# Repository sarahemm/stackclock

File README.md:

# stackclock
StackClock - Modular configurable high-accuracy desk clock

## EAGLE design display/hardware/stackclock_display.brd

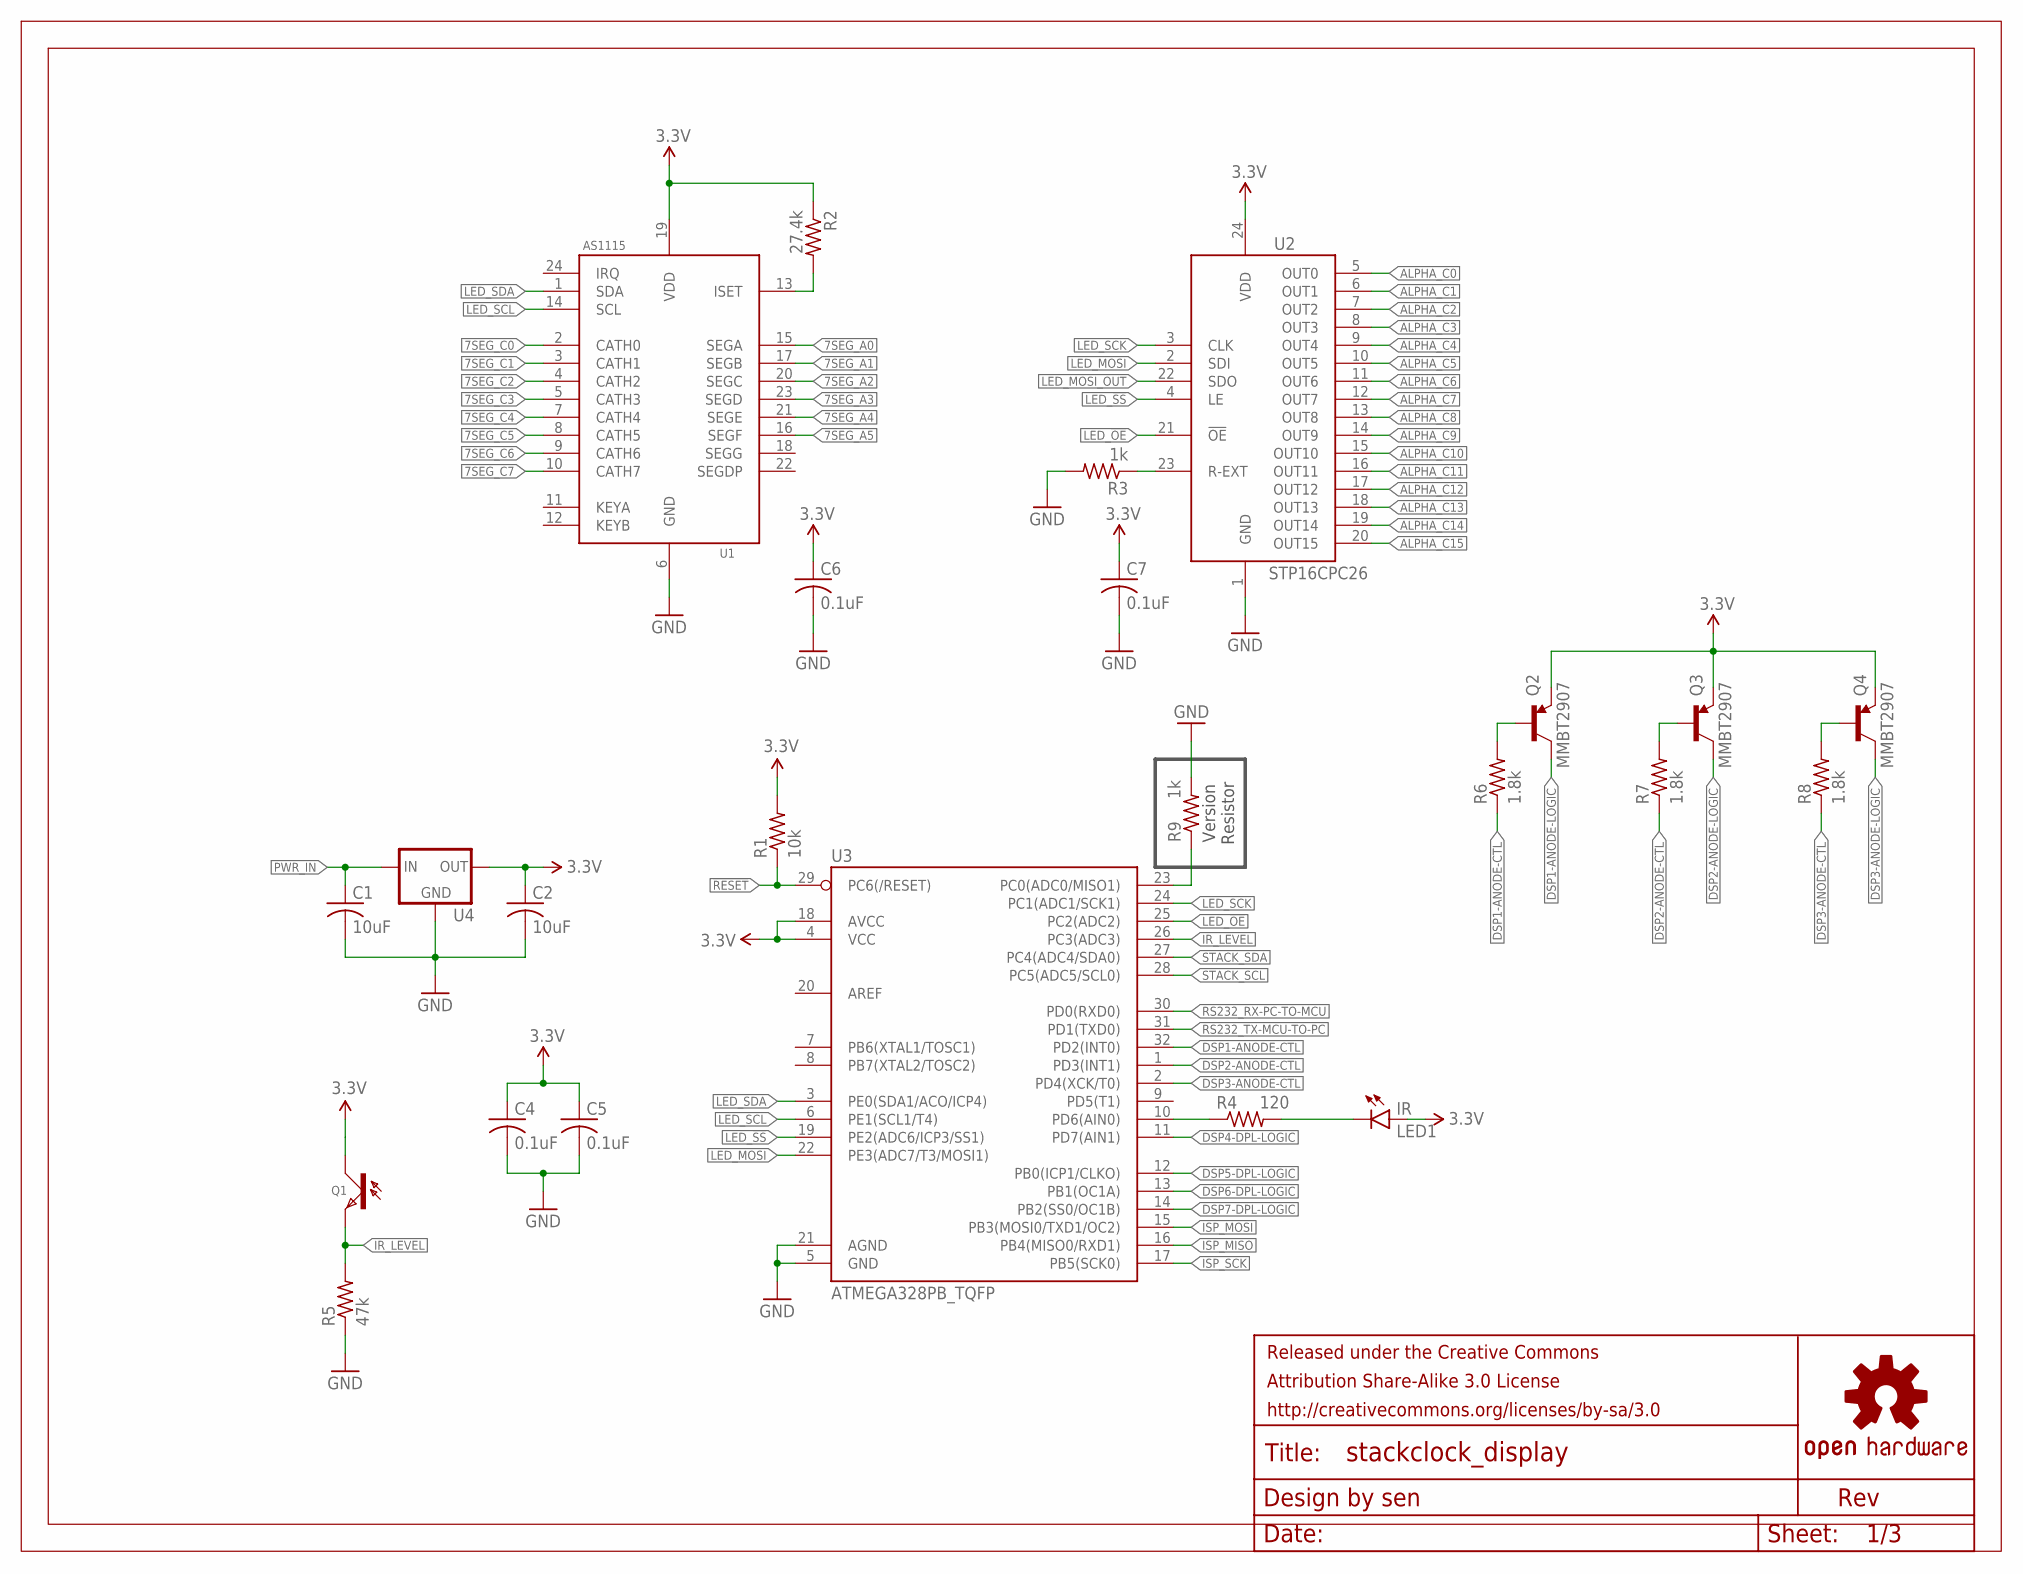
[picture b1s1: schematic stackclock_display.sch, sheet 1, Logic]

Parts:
C1, C2: 10uF; C0805
C4, C5, C6, C7: 0.1uF; C0603
FRAME1: FRAME-LETTER-GRID-OSHW-SENOSHW-LOGO-L; OSHW-LOGO-L
LED1: IR; LED-1206
Q1: PT15-21C/TR8; 1206_PHOTOTRANSISTOR
Q2, Q3, Q4: MMBT2907; SOT23-3
R1: 10k; R0603
R2: 27.4k; R0603
R3, R9: 1k; R0603
R4: 120; R0603
R5: 47k; R0603
R6, R7, R8: 1.8k; R0603
U1: AS1115; QSOP24
U2: STP16CPC26; TSSOP24
U3: ATMEGA328PB_TQFP; TQFP32-08
U4: NCP1117DT33G; DPAK

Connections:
3.3V: C2.1, C4.1, C5.1, C6.1, C7.1, LED1.A, Q1.C, Q2.2 (E), Q3.2 (E), Q4.2 (E), R1.2, R2.1, U1.19 (VDD), U2.24 (VDD), U3.4 (VCC), U3.18 (AVCC), U4.4 (OUT); also elsewhere on the board
7SEG_A0: U1.15 (SEGA); also elsewhere on the board
7SEG_A1: U1.17 (SEGB); also elsewhere on the board
7SEG_A2: U1.20 (SEGC); also elsewhere on the board
7SEG_A3: U1.23 (SEGD); also elsewhere on the board
7SEG_A4: U1.21 (SEGE); also elsewhere on the board
7SEG_A5: U1.16 (SEGF); also elsewhere on the board
7SEG_C0: U1.2 (CATH0); also elsewhere on the board
7SEG_C1: U1.3 (CATH1); also elsewhere on the board
7SEG_C2: U1.4 (CATH2); also elsewhere on the board
7SEG_C3: U1.5 (CATH3); also elsewhere on the board
7SEG_C4: U1.7 (CATH4); also elsewhere on the board
7SEG_C5: U1.8 (CATH5); also elsewhere on the board
7SEG_C6: U1.9 (CATH6); also elsewhere on the board
7SEG_C7: U1.10 (CATH7); also elsewhere on the board
!RESET: R1.1, U3.29 (PC6(/RESET)); also elsewhere on the board
ALPHA_C0: U2.5 (OUT0); also elsewhere on the board
ALPHA_C1: U2.6 (OUT1); also elsewhere on the board
ALPHA_C2: U2.7 (OUT2); also elsewhere on the board
ALPHA_C3: U2.8 (OUT3); also elsewhere on the board
ALPHA_C4: U2.9 (OUT4); also elsewhere on the board
ALPHA_C5: U2.10 (OUT5); also elsewhere on the board
ALPHA_C6: U2.11 (OUT6); also elsewhere on the board
ALPHA_C7: U2.12 (OUT7); also elsewhere on the board
ALPHA_C8: U2.13 (OUT8); also elsewhere on the board
ALPHA_C9: U2.14 (OUT9); also elsewhere on the board
ALPHA_C10: U2.15 (OUT10); also elsewhere on the board
ALPHA_C11: U2.16 (OUT11); also elsewhere on the board
ALPHA_C12: U2.17 (OUT12); also elsewhere on the board
ALPHA_C13: U2.18 (OUT13); also elsewhere on the board
ALPHA_C14: U2.19 (OUT14); also elsewhere on the board
ALPHA_C15: U2.20 (OUT15); also elsewhere on the board
DSP1-ANODE-CTL: R6.1, U3.32 (PD2(INT0))
DSP1-ANODE-LOGIC: Q2.3 (C); also elsewhere on the board
DSP1-ANODE-QR: Q2.1 (B), R6.2
DSP2-ANODE-CTL: R7.1, U3.1 (PD3(INT1))
DSP2-ANODE-LOGIC: Q3.3 (C); also elsewhere on the board
DSP2-ANODE-QR: Q3.1 (B), R7.2
DSP3-ANODE-CTL: R8.1, U3.2 (PD4(XCK/T0))
DSP3-ANODE-LOGIC: Q4.3 (C); also elsewhere on the board
DSP3-ANODE-QR: Q4.1 (B), R8.2
DSP4-DPL-LOGIC: U3.11 (PD7(AIN1)); also elsewhere on the board
DSP5-DPL-LOGIC: U3.12 (PB0(ICP1/CLKO)); also elsewhere on the board
DSP6-DPL-LOGIC: U3.13 (PB1(OC1A)); also elsewhere on the board
DSP7-DPL-LOGIC: U3.14 (PB2(SS0/OC1B)); also elsewhere on the board
GND: C1.2, C2.2, C4.2, C5.2, C6.2, C7.2, R3.2, R5.1, R9.2, U1.6 (GND), U2.1 (GND), U3.5 (GND), U3.21 (AGND), U4.1 (GND); also elsewhere on the board
HW_VERSION: R9.1, U3.23 (PC0(ADC0/MISO1))
IR_CTL: R4.1, U3.10 (PD6(AIN0))
IR_LEVEL: Q1.E, R5.2, U3.26 (PC3(ADC3)); also elsewhere on the board
IR_R: LED1.C, R4.2
ISP_MISO: U3.16 (PB4(MISO0/RXD1)); also elsewhere on the board
ISP_MOSI: U3.15 (PB3(MOSI0/TXD1/OC2)); also elsewhere on the board
ISP_SCK: U3.17 (PB5(SCK0)); also elsewhere on the board
LED_!OE: U2.21 (!OE), U3.25 (PC2(ADC2)); also elsewhere on the board
LED_!SS: U2.4 (LE), U3.19 (PE2(ADC6/ICP3/SS1)); also elsewhere on the board
LED_MOSI: U2.2 (SDI), U3.22 (PE3(ADC7/T3/MOSI1)); also elsewhere on the board
LED_MOSI_OUT: U2.22 (SDO); also elsewhere on the board
LED_SCK: U2.3 (CLK), U3.24 (PC1(ADC1/SCK1)); also elsewhere on the board
LED_SCL: U1.14 (SCL), U3.6 (PE1(SCL1/T4)); also elsewhere on the board
LED_SDA: U1.1 (SDA), U3.3 (PE0(SDA1/ACO/ICP4)); also elsewhere on the board
PWR_IN: C1.1, U4.3 (IN); also elsewhere on the board
RS232_RX-PC-TO-MCU: U3.30 (PD0(RXD0)); also elsewhere on the board
RS232_TX-MCU-TO-PC: U3.31 (PD1(TXD0)); also elsewhere on the board
STACK_SCL: U3.28 (PC5(ADC5/SCL0)); also elsewhere on the board
STACK_SDA: U3.27 (PC4(ADC4/SDA0)); also elsewhere on the board
U1-ISET: R2.2, U1.13 (ISET)
U2-REXT: R3.1, U2.23 (R-EXT)

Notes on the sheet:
Version Resistor

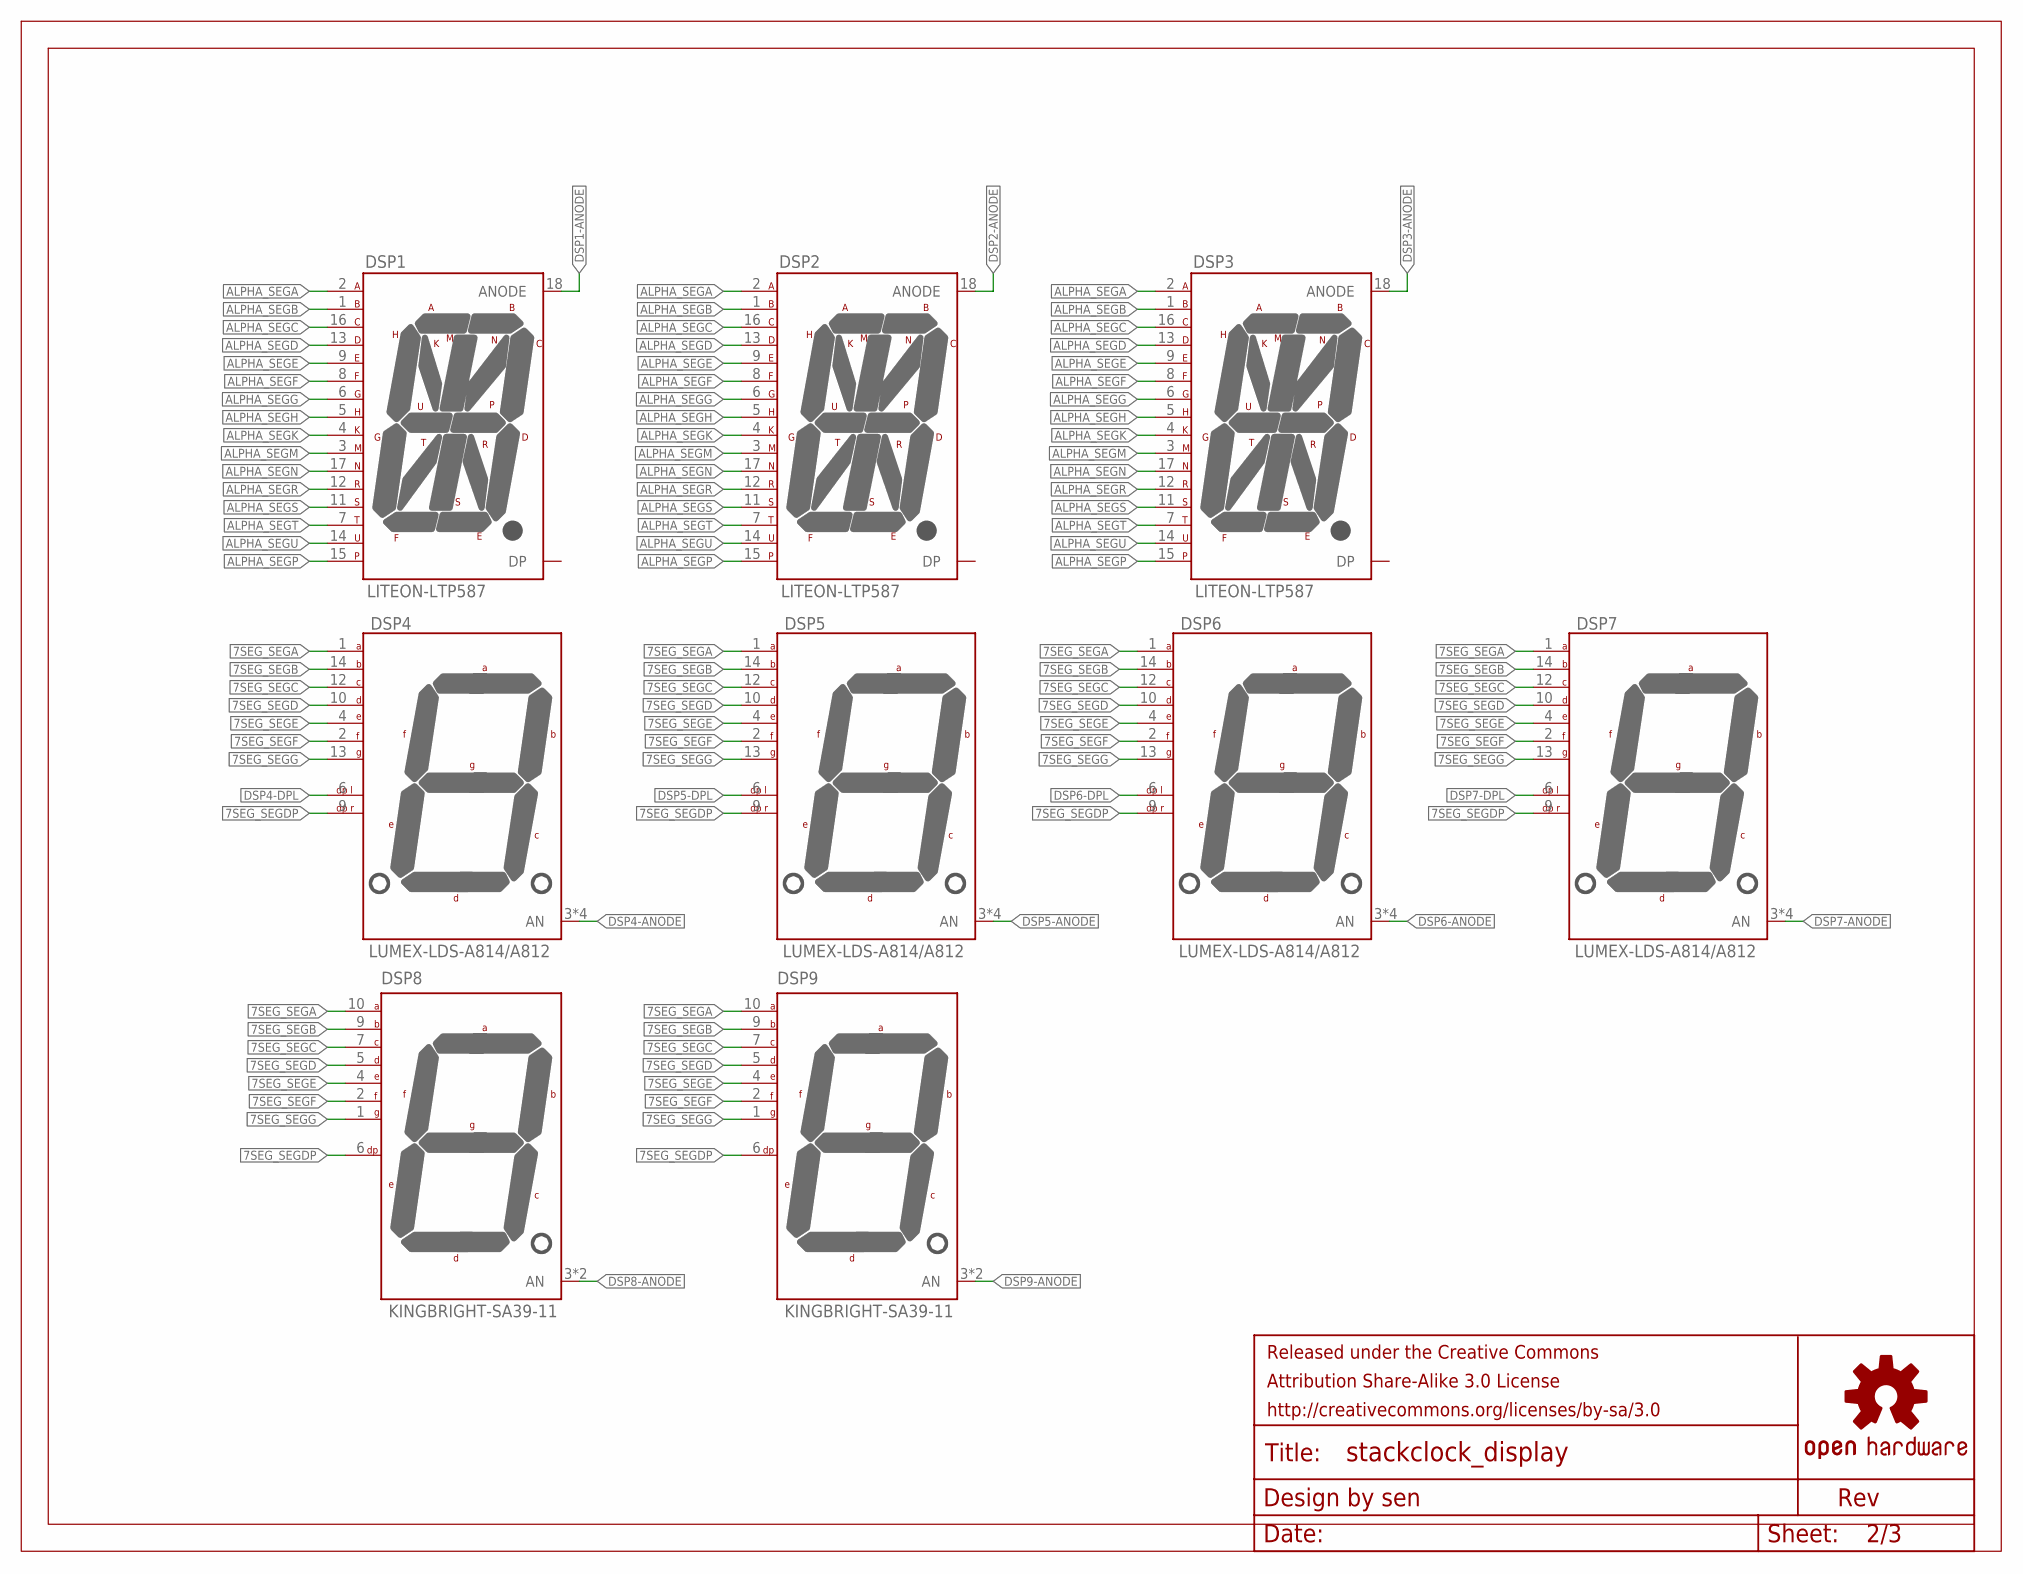
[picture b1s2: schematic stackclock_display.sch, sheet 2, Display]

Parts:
DSP1, DSP2, DSP3: LITEON-LTP587
DSP4, DSP5, DSP6, DSP7: LUMEX-LDS-A814/A812
DSP8, DSP9: KINGBRIGHT-SA39-11
FRAME2: FRAME-LETTER-GRID-OSHW-SENOSHW-LOGO-L; OSHW-LOGO-L

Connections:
7SEG_SEGA: DSP4.1 (A), DSP5.1 (A), DSP6.1 (A), DSP7.1 (A), DSP8.10 (A), DSP9.10 (A); also elsewhere on the board
7SEG_SEGB: DSP4.14 (B), DSP5.14 (B), DSP6.14 (B), DSP7.14 (B), DSP8.9 (B), DSP9.9 (B); also elsewhere on the board
7SEG_SEGC: DSP4.12 (C), DSP5.12 (C), DSP6.12 (C), DSP7.12 (C), DSP8.7 (C), DSP9.7 (C); also elsewhere on the board
7SEG_SEGD: DSP4.10 (D), DSP5.10 (D), DSP6.10 (D), DSP7.10 (D), DSP8.5 (D), DSP9.5 (D); also elsewhere on the board
7SEG_SEGDP: DSP4.9 (DP-R), DSP5.9 (DP-R), DSP6.9 (DP-R), DSP7.9 (DP-R), DSP8.6 (DP), DSP9.6 (DP); also elsewhere on the board
7SEG_SEGE: DSP4.4 (E), DSP5.4 (E), DSP6.4 (E), DSP7.4 (E), DSP8.4 (E), DSP9.4 (E); also elsewhere on the board
7SEG_SEGF: DSP4.2 (F), DSP5.2 (F), DSP6.2 (F), DSP7.2 (F), DSP8.2 (F), DSP9.2 (F); also elsewhere on the board
7SEG_SEGG: DSP4.13 (G), DSP5.13 (G), DSP6.13 (G), DSP7.13 (G), DSP8.1 (G), DSP9.1 (G); also elsewhere on the board
ALPHA_SEGA: DSP1.2 (A), DSP2.2 (A), DSP3.2 (A); also elsewhere on the board
ALPHA_SEGB: DSP1.1 (B), DSP2.1 (B), DSP3.1 (B); also elsewhere on the board
ALPHA_SEGC: DSP1.16 (C), DSP2.16 (C), DSP3.16 (C); also elsewhere on the board
ALPHA_SEGD: DSP1.13 (D), DSP2.13 (D), DSP3.13 (D); also elsewhere on the board
ALPHA_SEGE: DSP1.9 (E), DSP2.9 (E), DSP3.9 (E); also elsewhere on the board
ALPHA_SEGF: DSP1.8 (F), DSP2.8 (F), DSP3.8 (F); also elsewhere on the board
ALPHA_SEGG: DSP1.6 (G), DSP2.6 (G), DSP3.6 (G); also elsewhere on the board
ALPHA_SEGH: DSP1.5 (H), DSP2.5 (H), DSP3.5 (H); also elsewhere on the board
ALPHA_SEGK: DSP1.4 (K), DSP2.4 (K), DSP3.4 (K); also elsewhere on the board
ALPHA_SEGM: DSP1.3 (M), DSP2.3 (M), DSP3.3 (M); also elsewhere on the board
ALPHA_SEGN: DSP1.17 (N), DSP2.17 (N), DSP3.17 (N); also elsewhere on the board
ALPHA_SEGP: DSP1.15, DSP2.15, DSP3.15; also elsewhere on the board
ALPHA_SEGR: DSP1.12 (R), DSP2.12 (R), DSP3.12 (R); also elsewhere on the board
ALPHA_SEGS: DSP1.11 (S), DSP2.11 (S), DSP3.11 (S); also elsewhere on the board
ALPHA_SEGT: DSP1.7 (T), DSP2.7 (T), DSP3.7 (T); also elsewhere on the board
ALPHA_SEGU: DSP1.14 (U), DSP2.14 (U), DSP3.14 (U); also elsewhere on the board
DSP1-ANODE: DSP1.18 (ANODE); also elsewhere on the board
DSP2-ANODE: DSP2.18 (ANODE); also elsewhere on the board
DSP3-ANODE: DSP3.18 (ANODE); also elsewhere on the board
DSP4-ANODE: DSP4.3 (AN), DSP4.5 (AN), DSP4.11 (AN), DSP4.16 (AN); also elsewhere on the board
DSP4-DPL: DSP4.6 (DP-L); also elsewhere on the board
DSP5-ANODE: DSP5.3 (AN), DSP5.5 (AN), DSP5.11 (AN), DSP5.16 (AN); also elsewhere on the board
DSP5-DPL: DSP5.6 (DP-L); also elsewhere on the board
DSP6-ANODE: DSP6.3 (AN), DSP6.5 (AN), DSP6.11 (AN), DSP6.16 (AN); also elsewhere on the board
DSP6-DPL: DSP6.6 (DP-L); also elsewhere on the board
DSP7-ANODE: DSP7.3 (AN), DSP7.5 (AN), DSP7.11 (AN), DSP7.16 (AN); also elsewhere on the board
DSP7-DPL: DSP7.6 (DP-L); also elsewhere on the board
DSP8-ANODE: DSP8.3 (AN), DSP8.8 (AN); also elsewhere on the board
DSP9-ANODE: DSP9.3 (AN), DSP9.8 (AN); also elsewhere on the board

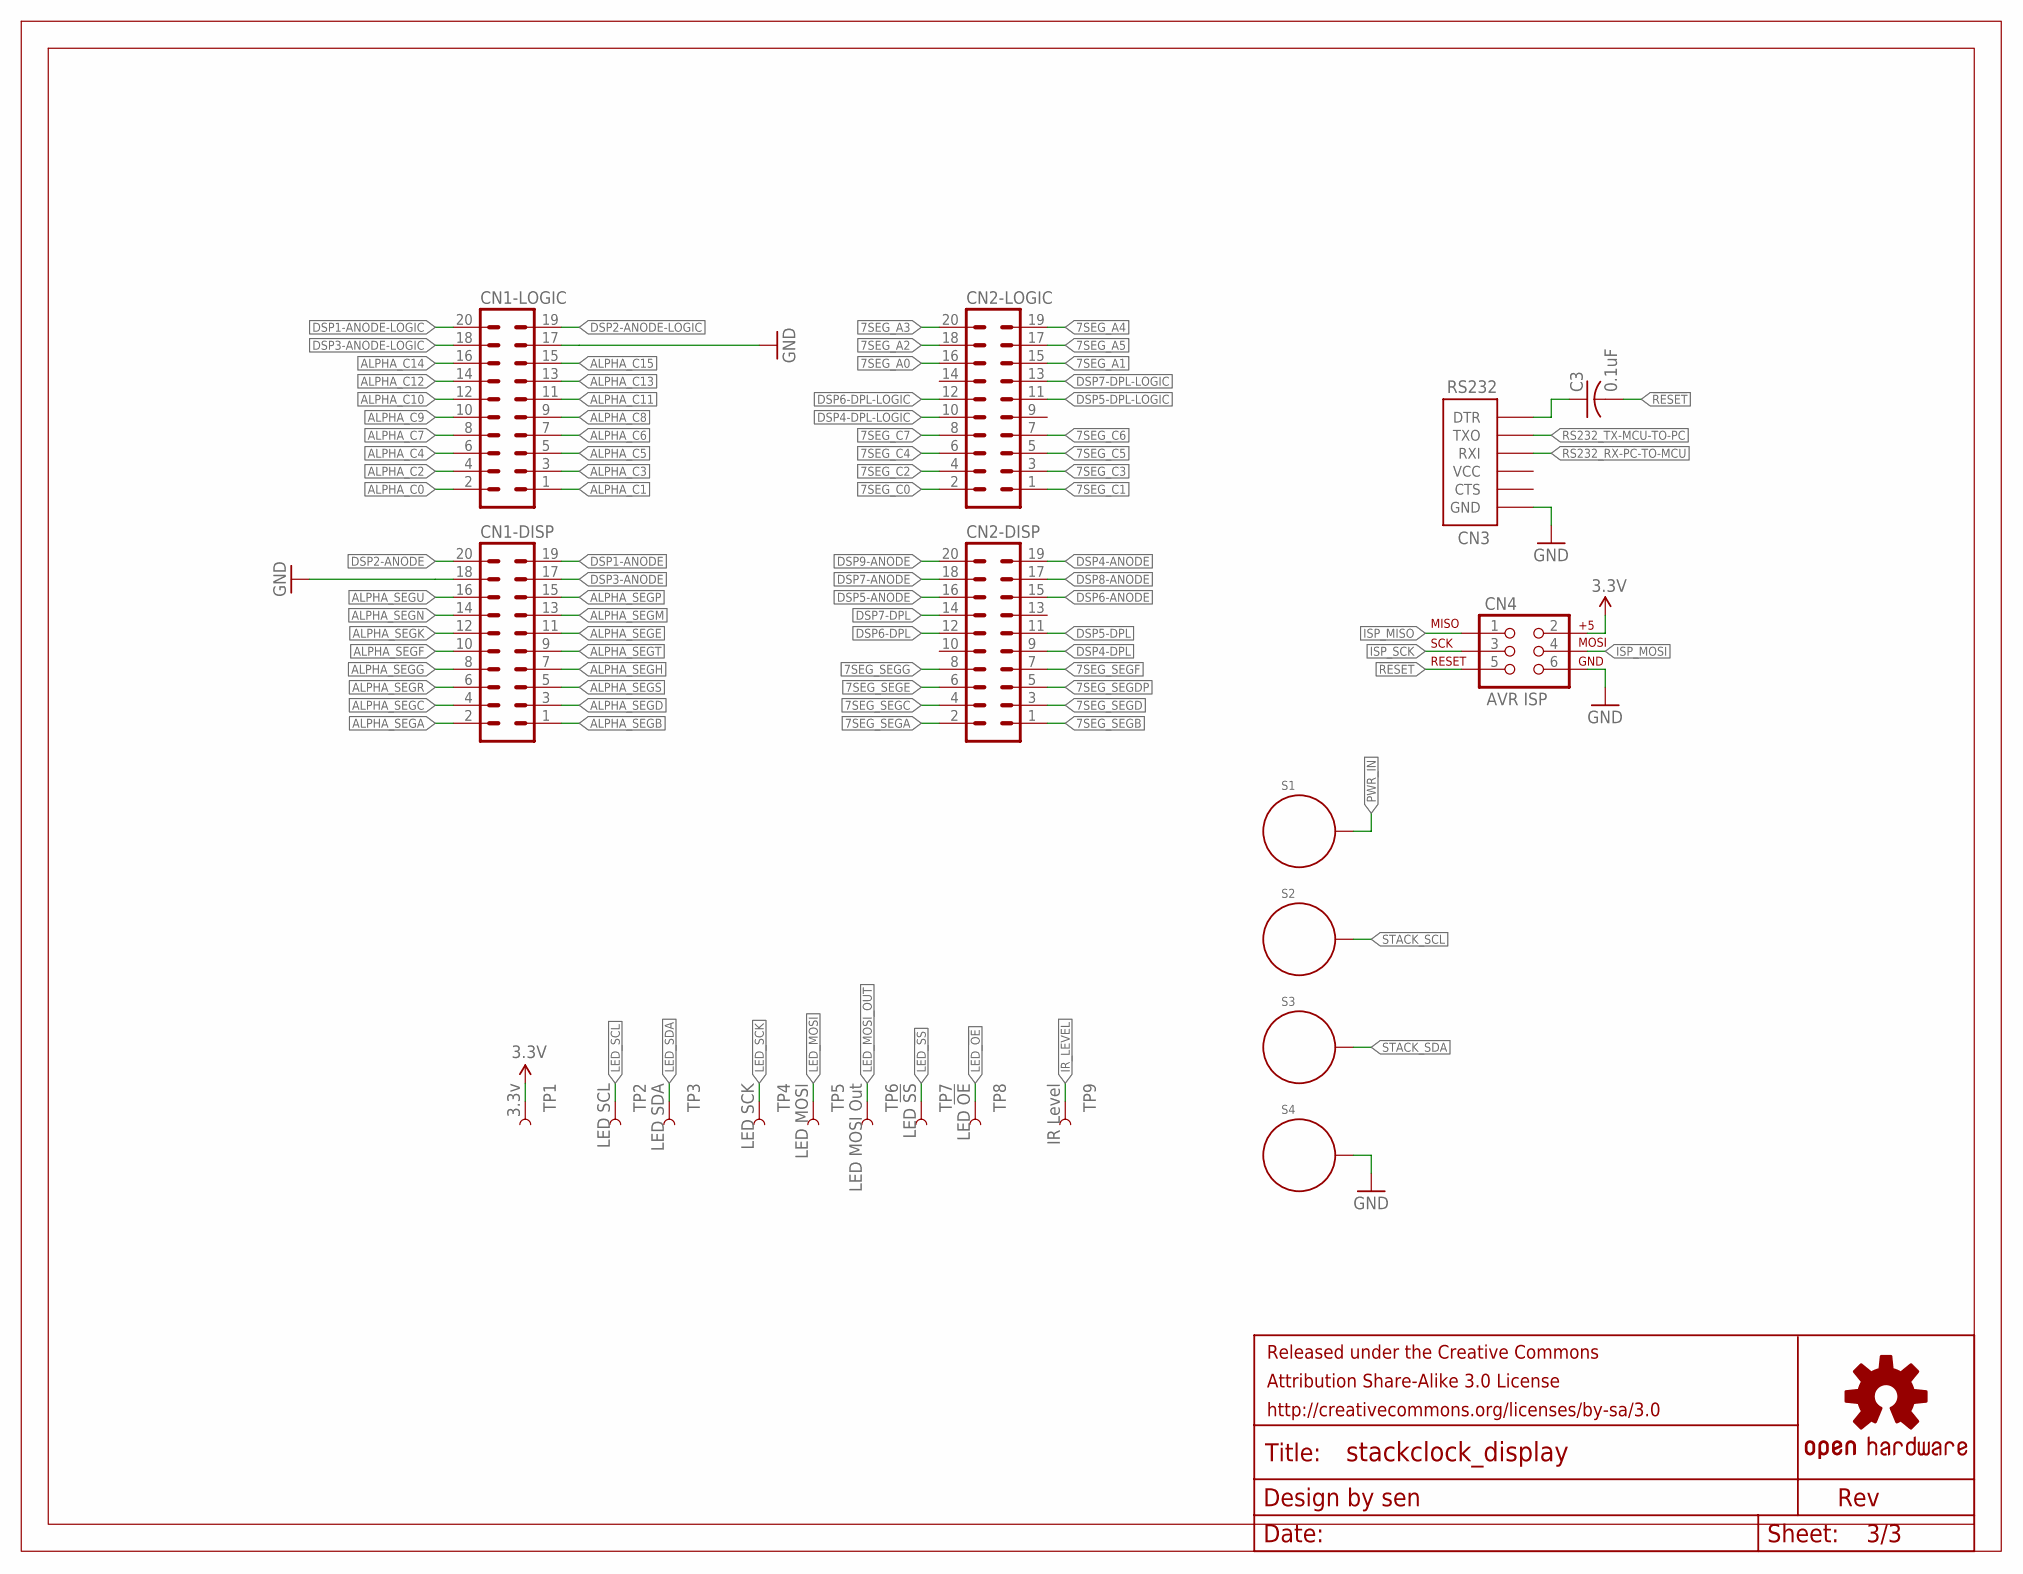
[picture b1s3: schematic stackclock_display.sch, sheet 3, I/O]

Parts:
C3: 0.1uF; C0603
CN1-DISP, CN2-DISP: MA10-2W
CN1-LOGIC, CN2-LOGIC: MA10-2
CN3: RS232; FTDI_DEVICE_SIDE
CN4: AVR ISP; 2X3_LOCK
FRAME3: FRAME-LETTER-GRID-OSHW-SENOSHW-LOGO-L; OSHW-LOGO-L
S1: +V; STANDOFF-ELECTRICAL
S2: SCL; STANDOFF-ELECTRICAL
S3: SDA; STANDOFF-ELECTRICAL
S4: GND; STANDOFF-ELECTRICAL
TP1: 3.3v; TP_15TH
TP2: LED SCL; TP_15TH
TP3: LED SDA; TP_15TH
TP4: LED SCK; TP_15TH
TP5: LED MOSI; TP_15TH
TP6: LED MOSI Out; TP_15TH
TP7: LED !SS; TP_15TH
TP8: LED !OE; TP_15TH
TP9: IR Level; TP_15TH

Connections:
3.3V: CN4.2, TP1.P$1; also elsewhere on the board
7SEG_A0: CN2-LOGIC.16; also elsewhere on the board
7SEG_A1: CN2-LOGIC.15; also elsewhere on the board
7SEG_A2: CN2-LOGIC.18; also elsewhere on the board
7SEG_A3: CN2-LOGIC.20; also elsewhere on the board
7SEG_A4: CN2-LOGIC.19; also elsewhere on the board
7SEG_A5: CN2-LOGIC.17; also elsewhere on the board
7SEG_C0: CN2-LOGIC.2; also elsewhere on the board
7SEG_C1: CN2-LOGIC.1; also elsewhere on the board
7SEG_C2: CN2-LOGIC.4; also elsewhere on the board
7SEG_C3: CN2-LOGIC.3; also elsewhere on the board
7SEG_C4: CN2-LOGIC.6; also elsewhere on the board
7SEG_C5: CN2-LOGIC.5; also elsewhere on the board
7SEG_C6: CN2-LOGIC.7; also elsewhere on the board
7SEG_C7: CN2-LOGIC.8; also elsewhere on the board
7SEG_SEGA: CN2-DISP.2; also elsewhere on the board
7SEG_SEGB: CN2-DISP.1; also elsewhere on the board
7SEG_SEGC: CN2-DISP.4; also elsewhere on the board
7SEG_SEGD: CN2-DISP.3; also elsewhere on the board
7SEG_SEGDP: CN2-DISP.5; also elsewhere on the board
7SEG_SEGE: CN2-DISP.6; also elsewhere on the board
7SEG_SEGF: CN2-DISP.7; also elsewhere on the board
7SEG_SEGG: CN2-DISP.8; also elsewhere on the board
!RESET: C3.2, CN4.5; also elsewhere on the board
ALPHA_C0: CN1-LOGIC.2; also elsewhere on the board
ALPHA_C1: CN1-LOGIC.1; also elsewhere on the board
ALPHA_C2: CN1-LOGIC.4; also elsewhere on the board
ALPHA_C3: CN1-LOGIC.3; also elsewhere on the board
ALPHA_C4: CN1-LOGIC.6; also elsewhere on the board
ALPHA_C5: CN1-LOGIC.5; also elsewhere on the board
ALPHA_C6: CN1-LOGIC.7; also elsewhere on the board
ALPHA_C7: CN1-LOGIC.8; also elsewhere on the board
ALPHA_C8: CN1-LOGIC.9; also elsewhere on the board
ALPHA_C9: CN1-LOGIC.10; also elsewhere on the board
ALPHA_C10: CN1-LOGIC.12; also elsewhere on the board
ALPHA_C11: CN1-LOGIC.11; also elsewhere on the board
ALPHA_C12: CN1-LOGIC.14; also elsewhere on the board
ALPHA_C13: CN1-LOGIC.13; also elsewhere on the board
ALPHA_C14: CN1-LOGIC.16; also elsewhere on the board
ALPHA_C15: CN1-LOGIC.15; also elsewhere on the board
ALPHA_SEGA: CN1-DISP.2; also elsewhere on the board
ALPHA_SEGB: CN1-DISP.1; also elsewhere on the board
ALPHA_SEGC: CN1-DISP.4; also elsewhere on the board
ALPHA_SEGD: CN1-DISP.3; also elsewhere on the board
ALPHA_SEGE: CN1-DISP.11; also elsewhere on the board
ALPHA_SEGF: CN1-DISP.10; also elsewhere on the board
ALPHA_SEGG: CN1-DISP.8; also elsewhere on the board
ALPHA_SEGH: CN1-DISP.7; also elsewhere on the board
ALPHA_SEGK: CN1-DISP.12; also elsewhere on the board
ALPHA_SEGM: CN1-DISP.13; also elsewhere on the board
ALPHA_SEGN: CN1-DISP.14; also elsewhere on the board
ALPHA_SEGP: CN1-DISP.15; also elsewhere on the board
ALPHA_SEGR: CN1-DISP.6; also elsewhere on the board
ALPHA_SEGS: CN1-DISP.5; also elsewhere on the board
ALPHA_SEGT: CN1-DISP.9; also elsewhere on the board
ALPHA_SEGU: CN1-DISP.16; also elsewhere on the board
DSP1-ANODE: CN1-DISP.19; also elsewhere on the board
DSP1-ANODE-LOGIC: CN1-LOGIC.20; also elsewhere on the board
DSP2-ANODE: CN1-DISP.20; also elsewhere on the board
DSP2-ANODE-LOGIC: CN1-LOGIC.19; also elsewhere on the board
DSP3-ANODE: CN1-DISP.17; also elsewhere on the board
DSP3-ANODE-LOGIC: CN1-LOGIC.18; also elsewhere on the board
DSP4-ANODE: CN2-DISP.19; also elsewhere on the board
DSP4-DPL: CN2-DISP.9; also elsewhere on the board
DSP4-DPL-LOGIC: CN2-LOGIC.10; also elsewhere on the board
DSP5-ANODE: CN2-DISP.16; also elsewhere on the board
DSP5-DPL: CN2-DISP.11; also elsewhere on the board
DSP5-DPL-LOGIC: CN2-LOGIC.11; also elsewhere on the board
DSP6-ANODE: CN2-DISP.15; also elsewhere on the board
DSP6-DPL: CN2-DISP.12; also elsewhere on the board
DSP6-DPL-LOGIC: CN2-LOGIC.12; also elsewhere on the board
DSP7-ANODE: CN2-DISP.18; also elsewhere on the board
DSP7-DPL: CN2-DISP.14; also elsewhere on the board
DSP7-DPL-LOGIC: CN2-LOGIC.13; also elsewhere on the board
DSP8-ANODE: CN2-DISP.17; also elsewhere on the board
DSP9-ANODE: CN2-DISP.20; also elsewhere on the board
GND: CN1-DISP.18, CN1-LOGIC.17, CN3.P$6 (GND), CN4.6, S4.P1; also elsewhere on the board
IR_LEVEL: TP9.P$1; also elsewhere on the board
ISP_MISO: CN4.1; also elsewhere on the board
ISP_MOSI: CN4.4; also elsewhere on the board
ISP_SCK: CN4.3; also elsewhere on the board
LED_!OE: TP8.P$1; also elsewhere on the board
LED_!SS: TP7.P$1; also elsewhere on the board
LED_MOSI: TP5.P$1; also elsewhere on the board
LED_MOSI_OUT: TP6.P$1; also elsewhere on the board
LED_SCK: TP4.P$1; also elsewhere on the board
LED_SCL: TP2.P$1; also elsewhere on the board
LED_SDA: TP3.P$1; also elsewhere on the board
PWR_IN: S1.P1; also elsewhere on the board
RS232_DTR: C3.1, CN3.P$1 (DTR)
RS232_RX-PC-TO-MCU: CN3.P$3 (RXI); also elsewhere on the board
RS232_TX-MCU-TO-PC: CN3.P$2 (TXO); also elsewhere on the board
STACK_SCL: S2.P1; also elsewhere on the board
STACK_SDA: S3.P1; also elsewhere on the board

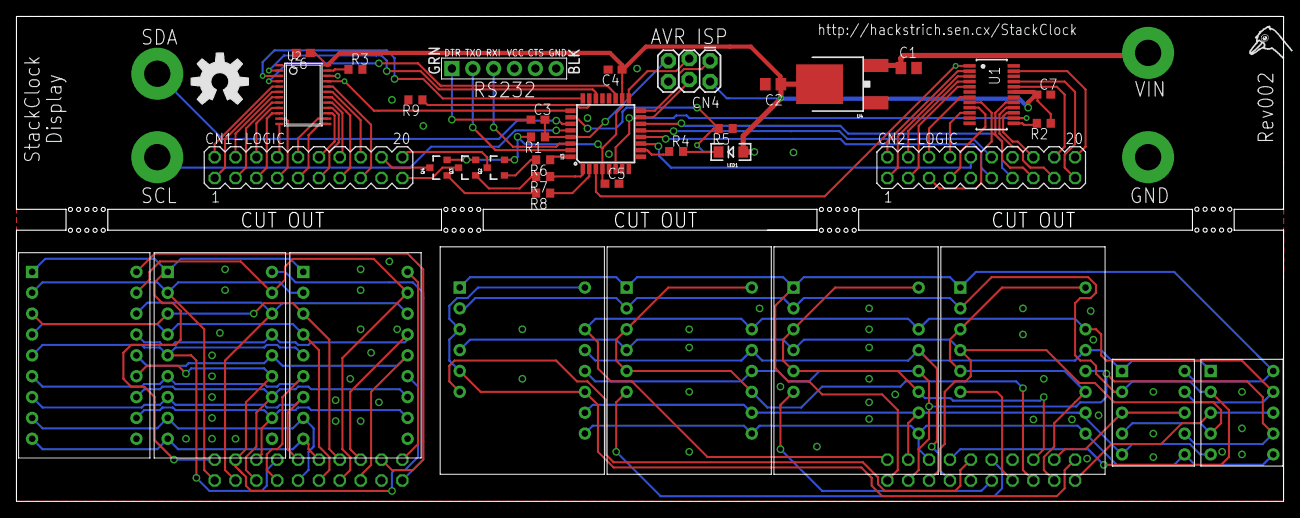
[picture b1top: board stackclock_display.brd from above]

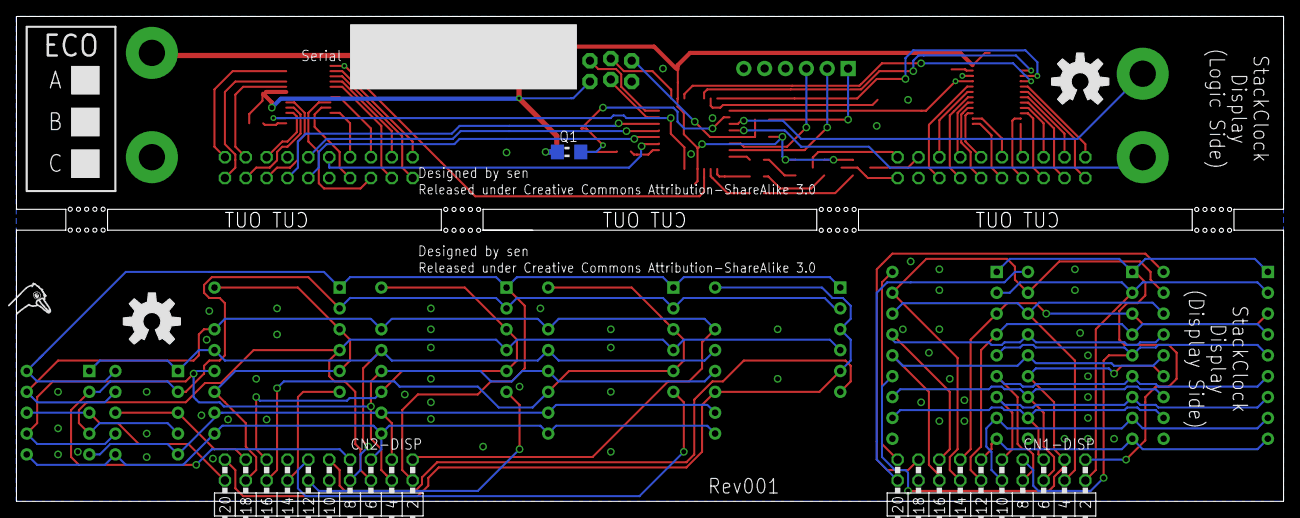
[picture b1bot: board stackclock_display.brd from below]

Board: 2 copper layers, 154.3 x 59.0 mm, 58 parts (15 on the bottom side), 105 nets.

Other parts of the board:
U$1: STRICH-LOGO-R
U$2: STRICH-LOGO

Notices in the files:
base/hardware/stackclock_base.brd:
Released under Creative Commons Attribution-ShareAlike 3.0
parts and their libraries:
SparkFun-DigitalIC: Licensing: Creative Commons ShareAlike 4.0 International - https://creativecommons.org/licenses/by-sa/4.0
logos-sen: Released under the Creative Commons Attribution Share-Alike 3.0 License
logos-sen: http://creativecommons.org/licenses/by-sa/3.0
